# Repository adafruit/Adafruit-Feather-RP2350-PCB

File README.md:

## Adafruit Feather RP2350 PCB

<a href="http://www.adafruit.com/products/6000"><br/>
Click here to purchase one from the Adafruit shop</a>

PCB files for the Adafruit Feather RP2350. 

Format is EagleCAD schematic and board layout
* https://www.adafruit.com/product/6000

### Description

RP2350 flies high with the Feather format - now you can use any FeatherWings with this battery-powered dev board. It comes with 8MB of flash, 22pin HSTX output port, Stemma QT, debug SWD, and optional PSRAM spot.

(more soooon!)

Please note: The Adafruit Feather RP2350 HSTX comes with the A2 version of the RP2350, which is affected by the E9 erratum. This errata affects some uses of GPIO and PIO such as high-impedance inputs and the internal pulldowns. You may need to use 8.2K or smaller resistors if pull-downs are required. At this time, Sept 9 2024, there is no other version of the RP2350 available - only the A2 version.

### License

Adafruit invests time and resources providing this open source design, please support Adafruit and open-source hardware by purchasing products from [Adafruit](https://www.adafruit.com)!

Designed by Limor Fried/Ladyada for Adafruit Industries.

Creative Commons Attribution/Share-Alike, all text above must be included in any redistribution. 
See license.txt for additional details.

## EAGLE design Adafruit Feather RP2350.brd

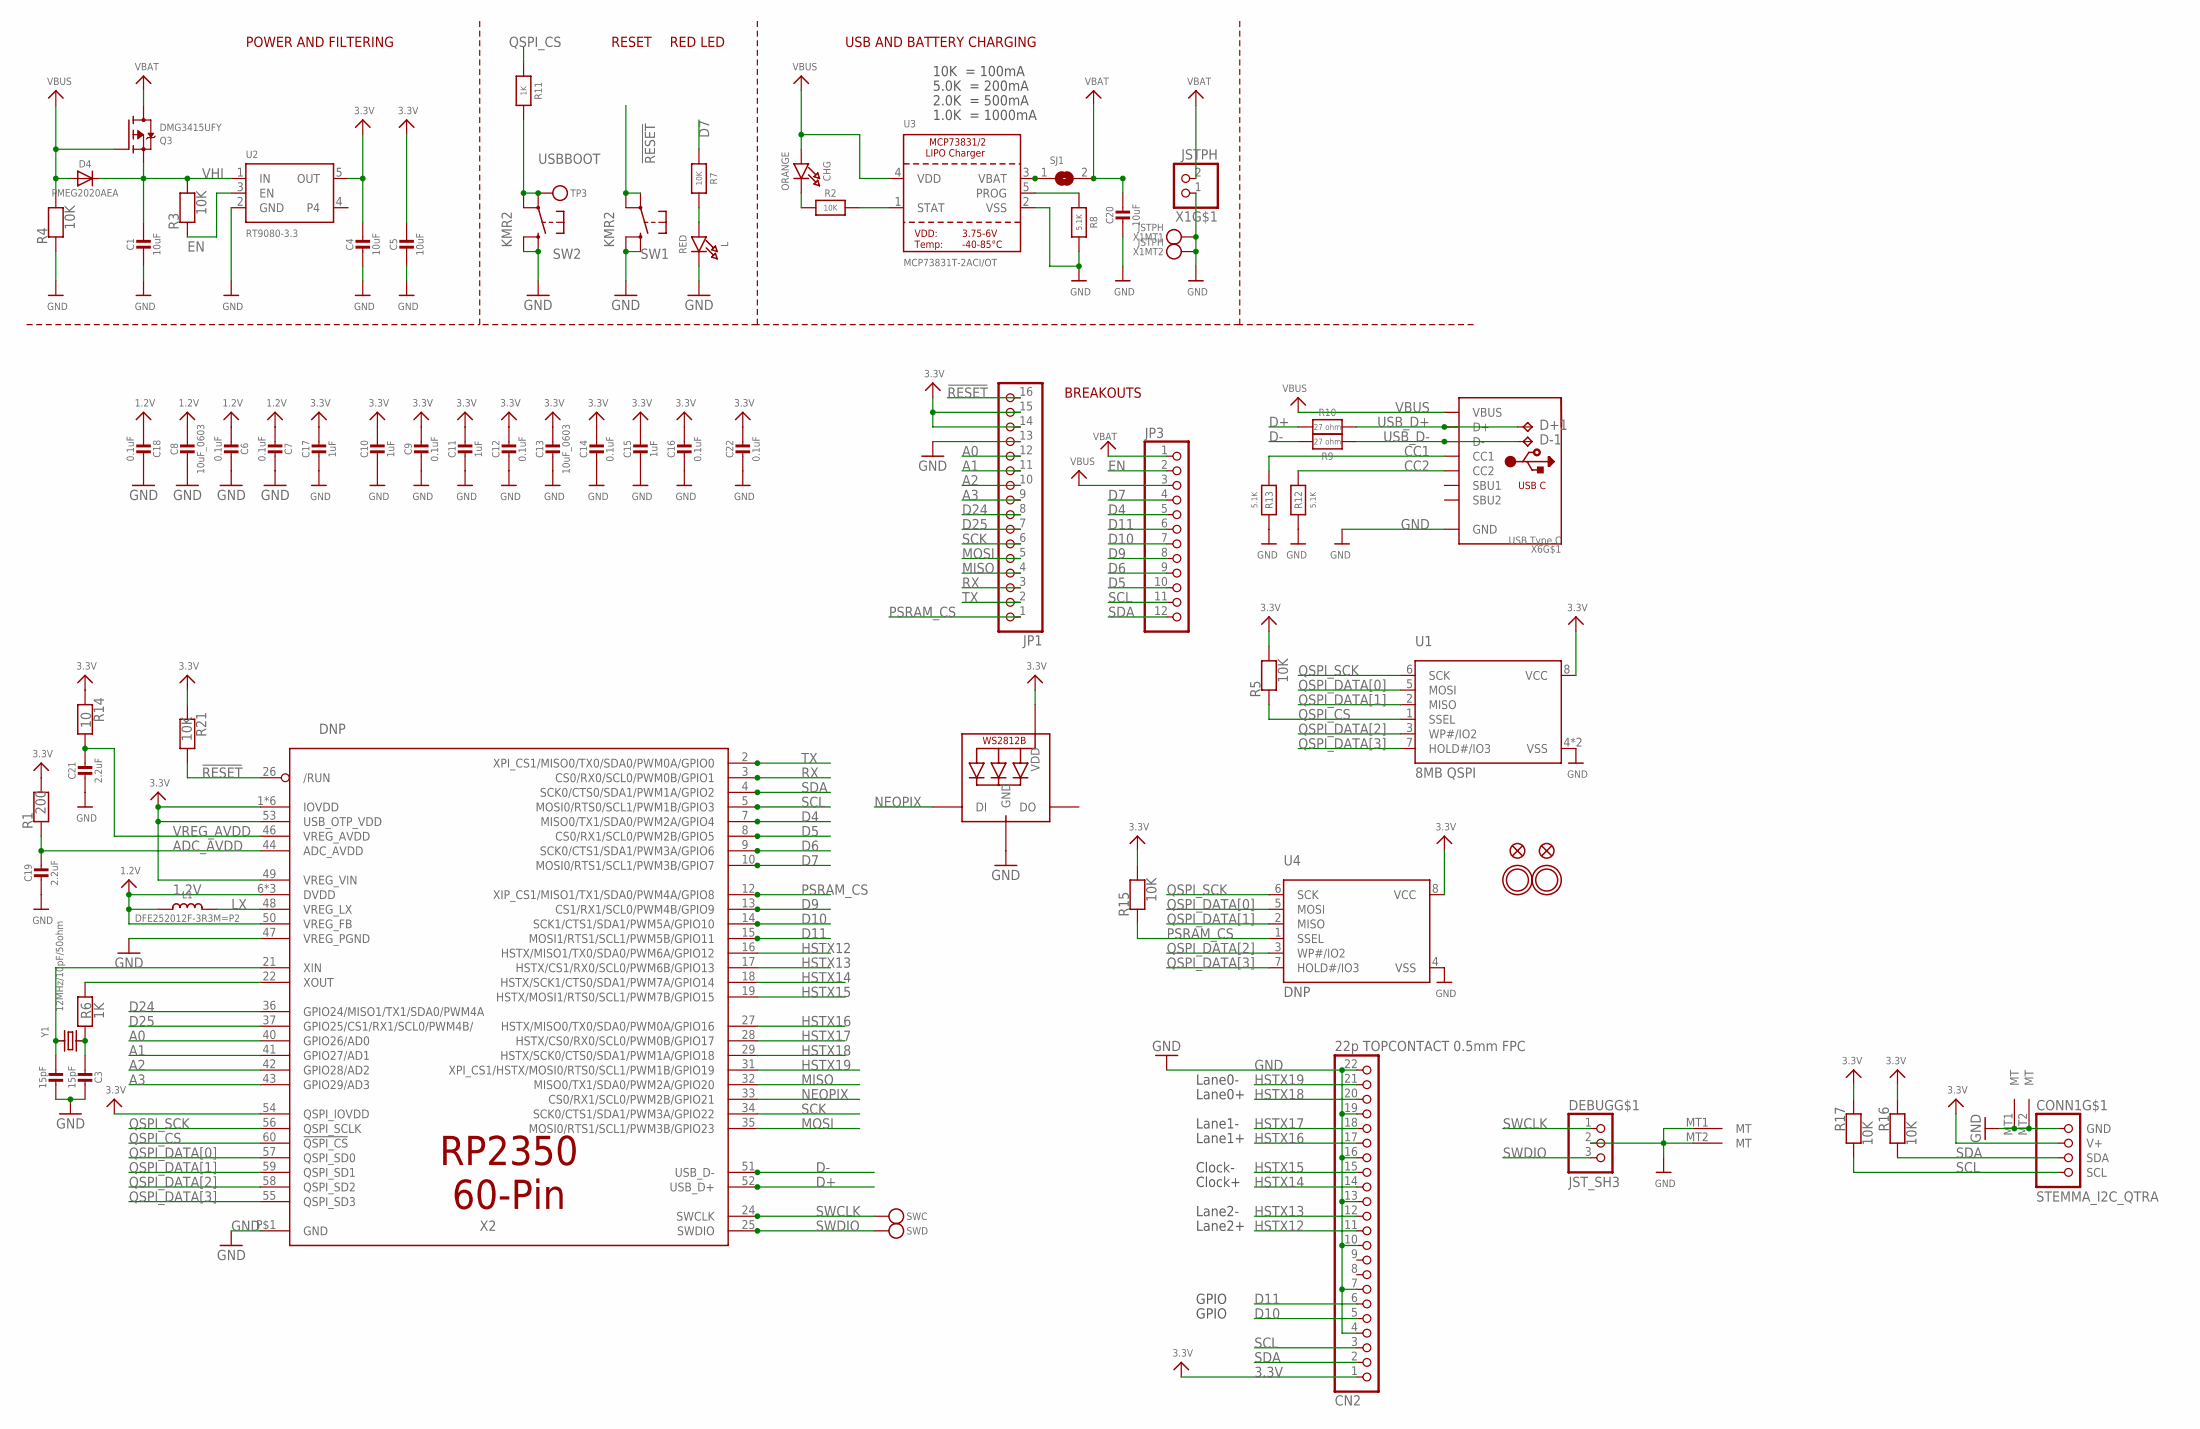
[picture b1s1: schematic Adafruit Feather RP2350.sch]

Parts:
C1, C4, C20: 10uF; 0805-NO
C2, C3: 15pF; _0402NO
C5: 10uF; 0603-NO
C6, C7, C9, C12, C14, C16, C18, C22: 0.1uF; _0402NO
C8, C13: 10uF_0603; _0603MP
C10, C11, C15, C17: 1uF; _0402NO
C19, C21: 2.2uF; _0402NO
CHG: ORANGE; CHIPLED_0603_NOOUTLINE
CN2: 22p TOPCONTACT 0.5mm FPC; FPC_22PIN
CONN1: STEMMA_I2C_QTRA; JST_SH4_RA
D4: PMEG2020AEA; SOD-323F
D+1: TPB1,27; B1,27
D-1: TPB1,27; B1,27
DEBUG: JST_SH3; JST_SH3_RA
JP1: HEADER-1X16ROUND; 1X16_ROUND
JP3: HEADER-1X12; 1X12_ROUND
L: RED; CHIPLED_0603_NOOUTLINE
L1: DFE252012F-3R3M=P2; INDUCTOR_1007
LED1: WS2812B_SK6805_1515; SK6805_1515
Q3: DMG3415UFY; DFN2015-3
R1: 200; _0402NO
R2, R3, R4, R5, R7, R15, R16, R17, R21: 10K; _0402NO
R6, R11: 1K; _0402NO
R8, R12, R13: 5.1K; _0402NO
R9, R10: 27 ohm; _0402NO
R14: 10; _0402NO
SJ1: SOLDERJUMPERCLOSED; SOLDERJUMPER_CLOSEDWIRE
SW1, SW2: KMR2; BTN_RKB2_4.6X2.8
SWC: TESTPOINTROUND1MM; TESTPOINT_ROUND_1MM
SWD: TESTPOINTROUND1MM; TESTPOINT_ROUND_1MM
TP3: TESTPOINTROUND1.5MMNO; TESTPOINT_ROUND_1.5MM_NO
U1: 8MB QSPI; USON8_4X4
U2: RT9080-3.3; SOT23-5; JLC_ROTATION 0
U3: MCP73831T-2ACI/OT; SOT23-5
U4: DNP; SOIC8_150MIL
U$31, U$32: MOUNTINGHOLE2.5; MOUNTINGHOLE_2.5_PLATED
U$34, U$35: FIDUCIAL_1MM
X1: JSTPH; JSTPH2_BATT
X2: DNP; QFN60_7MM_REDUCEDEPAD
X6: USB Type C; USB_C_CUSB31-CFM2AX-01-X
Y1: 12MHz/10pF/50ohm; CRYSTAL_2.5X2

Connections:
1.2V: C6.2, C7.2, C8.1, C18.2, L1.P$1 (1), X2.6 (DVDD), X2.23 (DVDD), X2.39 (DVDD), X2.50 (VREG_FB)
3.3V: C4.1, C5.1, C9.1, C10.1, C11.1, C12.1, C13.1, C14.1, C15.1, C16.1, C17.1, C22.1, CN2.1, CONN1.2 (V+), JP1.14, JP1.15, LED1.2 (VDD), R1.2, R5.2, R14.1, R15.2, R16.1, R17.1, R21.1, U1.8 (VCC), U2.5 (OUT), U4.8 (VCC), X2.1 (IOVDD), X2.11 (IOVDD), X2.20 (IOVDD), X2.30 (IOVDD), X2.38 (IOVDD), X2.45 (IOVDD), X2.49 (VREG_VIN), X2.53 (USB_OTP_VDD), X2.54 (QSPI_IOVDD)
!RESET: JP1.16, R21.2, SW1.A, SW1.A' (P1), X2.26 (/RUN)
A0: JP1.12, X2.40 (GPIO26/AD0)
A1: JP1.11, X2.41 (GPIO27/AD1)
A2: JP1.10, X2.42 (GPIO28/AD2)
A3: JP1.9, X2.43 (GPIO29/AD3)
ADC_AVDD: C19.1, R1.1, X2.44 (ADC_AVDD)
CC1: R13.2, X6.A5 (CC1)
CC2: R12.2, X6.B5 (CC2)
D4: JP3.5, X2.7 (MISO0/TX1/SDA0/PWM2A/GPIO4)
D5: JP3.10, X2.8 (CS0/RX1/SCL0/PWM2B/GPIO5)
D6: JP3.9, X2.9 (SCK0/CTS1/SDA1/PWM3A/GPIO6)
D7: JP3.4, R7.1, X2.10 (MOSI0/RTS1/SCL1/PWM3B/GPIO7)
D9: JP3.8, X2.13 (CS1/RX1/SCL0/PWM4B/GPIO9)
D10: CN2.5, JP3.7, X2.14 (SCK1/CTS1/SDA1/PWM5A/GPIO10)
D11: CN2.6, JP3.6, X2.15 (MOSI1/RTS1/SCL1/PWM5B/GPIO11)
D24: JP1.8, X2.36 (GPIO24/MISO1/TX1/SDA0/PWM4A)
D25: JP1.7, X2.37 (GPIO25/CS1/RX1/SCL0/PWM4B/)
D+: R10.2, X2.52 (USB_D+)
D-: R9.2, X2.51 (USB_D-)
EN: JP3.2, R3.1, U2.3 (EN)
GND: C1.2, C2.1, C3.1, C4.2, C5.2, C6.1, C7.1, C8.2, C9.2, C10.2, C11.2, C12.2, C13.2, C14.2, C15.2, C16.2, C17.2, C18.1, C19.2, C20.2, C21.2, C22.2, CN2.4, CN2.7, CN2.10, CN2.13, CN2.16, CN2.19, CN2.22, CONN1.1 (GND), CONN1.MT1 (MT), CONN1.MT2 (MT), DEBUG.2, DEBUG.MT1 (MT), DEBUG.MT2 (MT), JP1.13, L.C, LED1.4 (GND), R4.1, R8.2, R12.1, R13.1, SW1.B (S), SW1.B' (S1), SW2.B (S), SW2.B' (S1), U1.4 (VSS), U1.PAD (VSS), U2.2 (GND), U3.2 (VSS), U4.4 (VSS), X1.1, X1.NC1, X1.NC2, X2.47 (VREG_PGND), X2.P$1 (GND), X6.A1B12 (GND), X6.B1A12 (GND)
HSTX12: CN2.11, X2.16 (HSTX/MISO1/TX0/SDA0/PWM6A/GPIO12)
HSTX13: CN2.12, X2.17 (HSTX/CS1/RX0/SCL0/PWM6B/GPIO13)
HSTX14: CN2.14, X2.18 (HSTX/SCK1/CTS0/SDA1/PWM7A/GPIO14)
HSTX15: CN2.15, X2.19 (HSTX/MOSI1/RTS0/SCL1/PWM7B/GPIO15)
HSTX16: CN2.17, X2.27 (HSTX/MISO0/TX0/SDA0/PWM0A/GPIO16)
HSTX17: CN2.18, X2.28 (HSTX/CS0/RX0/SCL0/PWM0B/GPIO17)
HSTX18: CN2.20, X2.29 (HSTX/SCK0/CTS0/SDA1/PWM1A/GPIO18)
HSTX19: CN2.21, X2.31 (XPI_CS1/HSTX/MOSI0/RTS0/SCL1/PWM1B/GPIO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)
LX: L1.P$2 (2), X2.48 (VREG_LX)
MISO: JP1.4, X2.32 (MISO0/TX1/SDA0/PWM2A/GPIO20)
MOSI: JP1.5, X2.35 (MOSI0/RTS1/SCL1/PWM3B/GPIO23)
unnamed: CHG.C, R2.1
unnamed: L.A, R7.2
unnamed: R2.2, U3.1 (STAT)
unnamed: R8.1, U3.5 (PROG)
unnamed: C2.2, X2.21 (XIN), Y1.3 (2)
unnamed: C3.2, R6.1, Y1.1
unnamed: R6.2, X2.22 (XOUT)
unnamed: SJ1.1, U3.3 (VBAT)
NEOPIX: LED1.1 (DI), X2.33 (CS0/RX1/SCL0/PWM2B/GPIO21)
PSRAM_CS: JP1.1, R15.1, U4.1 (SSEL), X2.12 (XIP_CS1/MISO1/TX1/SDA0/PWM4A/GPIO8)
QSPI_CS: R5.1, R11.1, U1.1 (SSEL), X2.60 (!QSPI_CS)
QSPI_DATA[0]: U1.5 (MOSI), U4.5 (MOSI), X2.57 (QSPI_SD0)
QSPI_DATA[1]: U1.2 (MISO), U4.2 (MISO), X2.59 (QSPI_SD1)
QSPI_DATA[2]: U1.3 (WP#/IO2), U4.3 (WP#/IO2), X2.58 (QSPI_SD2)
QSPI_DATA[3]: U1.7 (HOLD#/IO3), U4.7 (HOLD#/IO3), X2.55 (QSPI_SD3)
QSPI_SCK: U1.6 (SCK), U4.6 (SCK), X2.56 (QSPI_SCLK)
RX: JP1.3, X2.3 (CS0/RX0/SCL0/PWM0B/GPIO1)
SCK: JP1.6, X2.34 (SCK0/CTS1/SDA1/PWM3A/GPIO22)
SCL: CN2.3, CONN1.4 (SCL), JP3.11, R17.2, X2.5 (MOSI0/RTS0/SCL1/PWM1B/GPIO3)
SDA: CN2.2, CONN1.3 (SDA), JP3.12, R16.2, X2.4 (SCK0/CTS0/SDA1/PWM1A/GPIO2)
SWCLK: DEBUG.1, SWC.P$1, X2.24 (SWCLK)
SWDIO: DEBUG.3, SWD.P$1, X2.25 (SWDIO)
TX: JP1.2, X2.2 (XPI_CS1/MISO0/TX0/SDA0/PWM0A/GPIO0)
USBBOOT: R11.2, SW2.A, SW2.A' (P1), TP3.P$1
USB_D+: D+1.TP, R10.1, X6.A6 (D+), X6.B6 (D+)
USB_D-: D-1.TP, R9.1, X6.A7 (D-), X6.B7 (D-)
VBAT: C20.1, JP3.1, Q3.3 (D), SJ1.2, X1.2
VBUS: CHG.A, D4.A, JP3.3, Q3.1 (G), R4.2, U3.4 (VDD), X6.A4B9 (VBUS), X6.B4A9 (VBUS)
VHI: C1.1, D4.C, Q3.2 (S), R3.2, U2.1 (IN)
VREG_AVDD: C21.1, R14.2, X2.46 (VREG_AVDD)

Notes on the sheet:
POWER AND FILTERING
RESET
10K = 100mA
5.0K = 200mA
2.0K = 500mA
1.0K = 1000mA
USB AND BATTERY CHARGING
BREAKOUTS
RED LED
Lane0-
Lane0+
Lane1-
Lane1+
Clock-
Clock+
Lane2-
Lane2+
GPIO

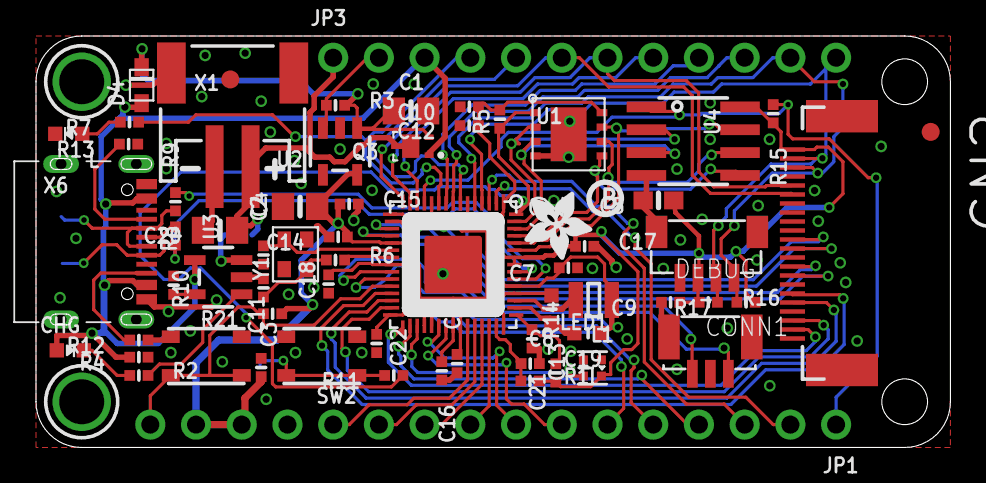
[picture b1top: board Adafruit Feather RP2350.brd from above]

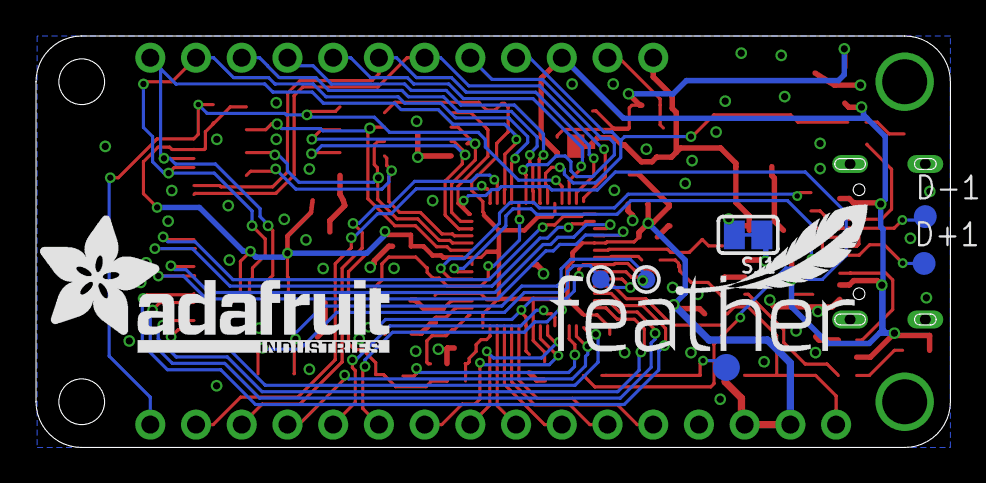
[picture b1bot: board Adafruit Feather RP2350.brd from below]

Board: 2 copper layers, 50.8 x 22.9 mm, 143 parts (39 on the bottom side), 64 nets.

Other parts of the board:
PLABEL0: PLABEL0
PLABEL1: PLABEL1
PLABEL2: PLABEL2
PLABEL3: PLABEL3
PLABEL4: PLABEL4
PLABEL5: PLABEL5
PLABEL6: PLABEL6
PLABEL7: PLABEL7
PLABEL8: PLABEL8
PLABEL9: PLABEL9
PLABEL10: PLABEL10
PLABEL11: PLABEL11
PLABEL12: PLABEL12
PLABEL13: PLABEL13
PLABEL14: PLABEL14
PLABEL15: PLABEL15
PLABEL16: PLABEL16
PLABEL17: PLABEL17
PLABEL18: PLABEL18
PLABEL19: PLABEL19
PLABEL20: PLABEL20
PLABEL21: PLABEL21
PLABEL22: PLABEL22
PLABEL23: PLABEL23
PLABEL24: PLABEL24
PLABEL25: PLABEL25
PLABEL26: PLABEL26
PLABEL27: PLABEL27
PLABEL28: PLABEL28
PLABEL29: PLABEL29
PLABEL30: PLABEL30
PLABEL31: PLABEL31
PLABEL32: PLABEL32
PLABEL33: PLABEL33
PLABEL34: PLABEL34
PLABEL35: PLABEL35
PLABEL36: PLABEL36
PLABEL37: PLABEL37
PLABEL38: PLABEL38
PLABEL39: PLABEL39
PLABEL40: PLABEL40
PLABEL41: PLABEL41
PLABEL42: PLABEL42
PLABEL43: PLABEL43
PLABEL44: PLABEL44
PLABEL45: PLABEL45
PLABEL46: PLABEL46
PLABEL47: PLABEL47
PLABEL48: PLABEL48
PLABEL49: PLABEL49
PLABEL50: PLABEL50
PLABEL51: PLABEL51
PLABEL52: PLABEL52
PLABEL53: PLABEL53
PLABEL54: PLABEL54
PLABEL55: PLABEL55
PLABEL56: PLABEL56
PLABEL57: PLABEL57
PLABEL58: PLABEL58
PLABEL59: PLABEL59
PLABEL60: PLABEL60
PLABEL61: PLABEL61
PLABEL62: PLABEL62
PLABEL63: PLABEL63
PLABEL64: PLABEL64
PLABEL65: PLABEL65
PLABEL67: PLABEL67
PLABEL68: PLABEL68
U$73: ADAFRUIT_3.5MM
U$74: PCBFEAT-REV-040
U$75: FEATHERLOGO_MED
U$76: ADAFRUIT_TEXT_20MM

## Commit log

2024-09-09 cookiecutter
2024-09-11 prettypins
2024-09-12 update prettypins
    D13 and D12
2024-11-18 update prettypins
    fix swapped stemma sda/scl gpio info

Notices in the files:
parts and their libraries:
microbuilder: This work is placed in the public domain, and may be freely used for commercial and non-commercial work with the following conditions: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
SparkFun-Aesthetics: Licensing: CC v3.0 Share-Alike You are welcome to use this library for commercial purposes.
